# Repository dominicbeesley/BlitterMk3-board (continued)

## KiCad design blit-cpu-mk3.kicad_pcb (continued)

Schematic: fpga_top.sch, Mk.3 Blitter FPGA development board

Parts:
U8: 10M16DCF256I7G_mk3pinstest; MAX10_FBGA_256_dom

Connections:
/ALTERA_CONFIG_SEL: U8.F8 (~ALTERA_CONFIG_SEL~); also elsewhere on the board
/ALTERA_CONF_DONE: U8.E7 (~ALTERA_CONF_DONE~); also elsewhere on the board
/ALTERA_nCONFIG: U8.E8 (~ALTERA_nCONFIG~); also elsewhere on the board
/ALTERA_nSTATUS: U8.F7 (~ALTERA_nSTATUS~); also elsewhere on the board
/CLK_48M: U8.J11 (CLK_48M_i); also elsewhere on the board
/HDMI_CKN: U8.P10 (HDMI_CK_o(n)); also elsewhere on the board
/HDMI_CKP: U8.P11 (HDMI_CK_o); also elsewhere on the board
/HDMI_D0N: U8.P13 (HDMI_D0_o(n)); also elsewhere on the board
/HDMI_D0P: U8.P12 (HDMI_D0_o); also elsewhere on the board
/HDMI_D1N: U8.M10 (HDMI_D1_o(n)); also elsewhere on the board
/HDMI_D1P: U8.L9 (HDMI_D1_o); also elsewhere on the board
/HDMI_D2N: U8.M11 (HDMI_D2_o(n)); also elsewhere on the board
/HDMI_D2P: U8.L10 (HDMI_D2_o); also elsewhere on the board
/HDMI_HPD: U8.T14 (HDMI_HPD_i); also elsewhere on the board
/HDMI_SCL: U8.T15 (HDMI_SCL_o); also elsewhere on the board
/HDMI_SDA: U8.R14 (HDMI_SDA_io); also elsewhere on the board
/I2C_SCL: U8.T8 (I2C_SCL_o); also elsewhere on the board
/I2C_SDA: U8.R9 (I2C_SDA_io); also elsewhere on the board
/MEM_FL_nCE: U8.B2 (MEM_FL_nCE_o); also elsewhere on the board
/MEM_RAM_nCE0: U8.F5 (MEM_RAM_nCE_o_0); also elsewhere on the board
/MEM_nOE: U8.C3 (MEM_nOE_o); also elsewhere on the board
/MEM_nWE: U8.K6 (MEM_nWE_o); also elsewhere on the board
/SD_CLK: U8.P9 (SD_CLK_o); also elsewhere on the board
/SD_CS: U8.R10 (SD_CS_o); also elsewhere on the board
/SD_DET: U8.T12 (SD_DET_i); also elsewhere on the board
/SD_MISO: U8.R11 (SD_MISO_i); also elsewhere on the board
/SD_MOSI: U8.T11 (SD_MOSI_o); also elsewhere on the board
/SND_L: U8.M9 (SND_L_o); also elsewhere on the board
/SND_R: U8.T9 (SND_R_o); also elsewhere on the board
/SUP_nRES: U8.R8 (SUP_nRESET_i); also elsewhere on the board
/SYS_BUFD_DIR: U8.E16 (SYS_BUF_D_DIR_o); also elsewhere on the board
/SYS_BUFD_nOE: U8.F14 (SYS_BUF_D_nOE_o); also elsewhere on the board
/SYS_DBE: U8.D16 (SYS_nDBE_i); also elsewhere on the board
/SYS_PHI0: U8.D15 (SYS_PHI0_i); also elsewhere on the board
/SYS_PHI1: U8.N16 (SYS_PHI1_o); also elsewhere on the board
/SYS_PHI2: U8.R15 (SYS_PHI2_o); also elsewhere on the board
/SYS_RDY: U8.C15 (SYS_RDY_i); also elsewhere on the board
/SYS_RnW: U8.M16 (SYS_RnW_o); also elsewhere on the board
/SYS_SYNC: U8.N14 (SYS_SYNC_o); also elsewhere on the board
/SYS_nIRQ: U8.C16 (SYS_nIRQ_i); also elsewhere on the board
/SYS_nNMI: U8.B15 (SYS_nNMI_i); also elsewhere on the board
/UI/LED0: U8.D14 (LED_o_0); also elsewhere on the board
/UI/LED1: U8.G11 (LED_o_1); also elsewhere on the board
/UI/LED2: U8.E14 (LED_o_2); also elsewhere on the board
/UI/LED3: U8.G12 (LED_o_3); also elsewhere on the board
/exp_PORTA_DIR: U8.C4 (exp_PORTA_DIR_o); also elsewhere on the board
/exp_PORTA_nOE: U8.C5 (exp_PORTA_nOE_o); also elsewhere on the board
/exp_PORTE_nOE: U8.A3 (exp_PORTE_nOE); also elsewhere on the board
/exp_PORTF_nOE: U8.B3 (exp_PORTF_nOE); also elsewhere on the board
/exp_PORTG_nOE: U8.B16 (exp_PORTG_nOE); also elsewhere on the board
/fpga_top/BTNUSER_i_0: U8.C14 (BTNUSER_i_0); also elsewhere on the board
/fpga_top/BTNUSER_i_1: U8.F12 (BTNUSER_i_1); also elsewhere on the board
/fpga_top/exp_PORTA_io_0: U8.C6 (exp_PORTA_io_0); also elsewhere on the board
/fpga_top/exp_PORTA_io_1: U8.E9 (exp_PORTA_io_1); also elsewhere on the board
/fpga_top/exp_PORTA_io_2: U8.F9 (exp_PORTA_io_2); also elsewhere on the board
/fpga_top/exp_PORTA_io_3: U8.C10 (exp_PORTA_io_3); also elsewhere on the board
/fpga_top/exp_PORTA_io_4: U8.E11 (exp_PORTA_io_4); also elsewhere on the board
/fpga_top/exp_PORTA_io_5: U8.C9 (exp_PORTA_io_5); also elsewhere on the board
/fpga_top/exp_PORTA_io_6: U8.D9 (exp_PORTA_io_6); also elsewhere on the board
/fpga_top/exp_PORTA_io_7: U8.B12 (exp_PORTA_io_7); also elsewhere on the board
/fpga_top/exp_PORTB_o_0: U8.C12 (exp_PORTB_o_0); also elsewhere on the board
/fpga_top/exp_PORTB_o_1: U8.D12 (exp_PORTB_o_1); also elsewhere on the board
/fpga_top/exp_PORTB_o_2: U8.C13 (exp_PORTB_o_2); also elsewhere on the board
/fpga_top/exp_PORTB_o_3: U8.A15 (exp_PORTB_o_3); also elsewhere on the board
/fpga_top/exp_PORTB_o_4: U8.A13 (exp_PORTB_o_4); also elsewhere on the board
/fpga_top/exp_PORTB_o_5: U8.B13 (exp_PORTB_o_5); also elsewhere on the board
/fpga_top/exp_PORTB_o_6: U8.A14 (exp_PORTB_o_6); also elsewhere on the board
/fpga_top/exp_PORTB_o_7: U8.F11 (exp_PORTB_o_7); also elsewhere on the board
/fpga_top/exp_PORTC_io_0: U8.R5 (exp_PORTC_io_0); also elsewhere on the board
/fpga_top/exp_PORTC_io_1: U8.T5 (exp_PORTC_io_1); also elsewhere on the board
/fpga_top/exp_PORTC_io_2: U8.R6 (exp_PORTC_io_2); also elsewhere on the board
/fpga_top/exp_PORTC_io_3: U8.R4 (exp_PORTC_io_3); also elsewhere on the board
/fpga_top/exp_PORTC_io_4: U8.T3 (exp_PORTC_io_4); also elsewhere on the board
/fpga_top/exp_PORTC_io_5: U8.T6 (exp_PORTC_io_5); also elsewhere on the board
/fpga_top/exp_PORTC_io_6: U8.R3 (exp_PORTC_io_6); also elsewhere on the board
/fpga_top/exp_PORTC_io_7: U8.T4 (exp_PORTC_io_7); also elsewhere on the board
/fpga_top/exp_PORTC_io_8: U8.P6 (exp_PORTC_io_8); also elsewhere on the board
/fpga_top/exp_PORTC_io_9: U8.P5 (exp_PORTC_io_9); also elsewhere on the board
/fpga_top/exp_PORTC_io_10: U8.P4 (exp_PORTC_io_10); also elsewhere on the board
/fpga_top/exp_PORTC_io_11: U8.N3 (exp_PORTC_io_11); also elsewhere on the board
/fpga_top/exp_PORTD_io_0: U8.N5 (exp_PORTD_io_0); also elsewhere on the board
/fpga_top/exp_PORTD_io_1: U8.N4 (exp_PORTD_io_1); also elsewhere on the board
/fpga_top/exp_PORTD_io_2: U8.R2 (exp_PORTD_io_2); also elsewhere on the board
/fpga_top/exp_PORTD_io_3: U8.M3 (exp_PORTD_io_3); also elsewhere on the board
/fpga_top/exp_PORTD_io_4: U8.M1 (exp_PORTD_io_4); also elsewhere on the board
/fpga_top/exp_PORTD_io_5: U8.M2 (exp_PORTD_io_5); also elsewhere on the board
/fpga_top/exp_PORTD_io_6: U8.T2 (exp_PORTD_io_6); also elsewhere on the board
/fpga_top/exp_PORTD_io_7: U8.N1 (exp_PORTD_io_7); also elsewhere on the board
/fpga_top/exp_PORTD_io_8: U8.N2 (exp_PORTD_io_8); also elsewhere on the board
/fpga_top/exp_PORTD_io_9: U8.R1 (exp_PORTD_io_9); also elsewhere on the board
/fpga_top/exp_PORTD_io_10: U8.P2 (exp_PORTD_io_10); also elsewhere on the board
/fpga_top/exp_PORTD_io_11: U8.P1 (exp_PORTD_io_11); also elsewhere on the board
/fpga_top/exp_PORTEFG_io_0: U8.A4 (exp_PORTEFG_io_0); also elsewhere on the board
/fpga_top/exp_PORTEFG_io_1: U8.B4 (exp_PORTEFG_io_1); also elsewhere on the board
/fpga_top/exp_PORTEFG_io_2: U8.A5 (exp_PORTEFG_io_2); also elsewhere on the board
/fpga_top/exp_PORTEFG_io_3: U8.B5 (exp_PORTEFG_io_3); also elsewhere on the board
/fpga_top/exp_PORTEFG_io_4: U8.A6 (exp_PORTEFG_io_4); also elsewhere on the board
/fpga_top/exp_PORTEFG_io_5: U8.B6 (exp_PORTEFG_io_5); also elsewhere on the board
/fpga_top/exp_PORTEFG_io_6: U8.A7 (exp_PORTEFG_io_6); also elsewhere on the board
/fpga_top/exp_PORTEFG_io_7: U8.B7 (exp_PORTEFG_io_7); also elsewhere on the board
/fpga_top/exp_PORTEFG_io_8: U8.A8 (exp_PORTEFG_io_8); also elsewhere on the board
/fpga_top/exp_PORTEFG_io_9: U8.B8 (exp_PORTEFG_io_9); also elsewhere on the board
/fpga_top/exp_PORTEFG_io_10: U8.A9 (exp_PORTEFG_io_10); also elsewhere on the board
/fpga_top/exp_PORTEFG_io_11: U8.B9 (exp_PORTEFG_io_11); also elsewhere on the board
/memory/MEM_A0: U8.F4 (MEM_A_o_0); also elsewhere on the board
/memory/MEM_A1: U8.G2 (MEM_A_o_1); also elsewhere on the board
/memory/MEM_A2: U8.J2 (MEM_A_o_2); also elsewhere on the board
/memory/MEM_A3: U8.J1 (MEM_A_o_3); also elsewhere on the board
/memory/MEM_A4: U8.L3 (MEM_A_o_4); also elsewhere on the board
/memory/MEM_A5: U8.L2 (MEM_A_o_5); also elsewhere on the board
/memory/MEM_A6: U8.L1 (MEM_A_o_6); also elsewhere on the board
/memory/MEM_A7: U8.L6 (MEM_A_o_7); also elsewhere on the board
/memory/MEM_A8: U8.H5 (MEM_A_o_8); also elsewhere on the board
/memory/MEM_A9: U8.H6 (MEM_A_o_9); also elsewhere on the board
/memory/MEM_A10: U8.A2 (MEM_A_o_10); also elsewhere on the board
/memory/MEM_A11: U8.G5 (MEM_A_o_11); also elsewhere on the board
/memory/MEM_A12: U8.L7 (MEM_A_o_12); also elsewhere on the board
/memory/MEM_A13: U8.J6 (MEM_A_o_13); also elsewhere on the board
/memory/MEM_A14: U8.J5 (MEM_A_o_14); also elsewhere on the board
/memory/MEM_A15: U8.L8 (MEM_A_o_15); also elsewhere on the board
/memory/MEM_A16: U8.K2 (MEM_A_o_16); also elsewhere on the board
/memory/MEM_A17: U8.J3 (MEM_A_o_17); also elsewhere on the board
/memory/MEM_A18: U8.K5 (MEM_A_o_18); also elsewhere on the board
/memory/MEM_A19: U8.T7 (MEM_A_o_19); also elsewhere on the board
/memory/MEM_A20: U8.R7 (MEM_A_o_20); also elsewhere on the board
/memory/MEM_D0: U8.F1 (MEM_D_io_0); also elsewhere on the board
/memory/MEM_D1: U8.F2 (MEM_D_io_1); also elsewhere on the board
/memory/MEM_D2: U8.E1 (MEM_D_io_2); also elsewhere on the board
/memory/MEM_D3: U8.E3 (MEM_D_io_3); also elsewhere on the board
/memory/MEM_D4: U8.D1 (MEM_D_io_4); also elsewhere on the board
/memory/MEM_D5: U8.C1 (MEM_D_io_5); also elsewhere on the board
/memory/MEM_D6: U8.C2 (MEM_D_io_6); also elsewhere on the board
/memory/MEM_D7: U8.B1 (MEM_D_io_7); also elsewhere on the board
/memory/MEM_RAM_nCE1: U8.G6 (MEM_RAM_nCE_o_1); also elsewhere on the board
/memory/MEM_RAM_nCE2: U8.M6 (MEM_RAM_nCE_o_2); also elsewhere on the board
/memory/MEM_RAM_nCE3: U8.M8 (MEM_RAM_nCE_o_3); also elsewhere on the board
/sys_plug_and_buffers/SYS_A0: U8.M14 (SYS_A_o_0); also elsewhere on the board
/sys_plug_and_buffers/SYS_A1: U8.M15 (SYS_A_o_1); also elsewhere on the board
/sys_plug_and_buffers/SYS_A2: U8.L12 (SYS_A_o_2); also elsewhere on the board
/sys_plug_and_buffers/SYS_A3: U8.K14 (SYS_A_o_3); also elsewhere on the board
/sys_plug_and_buffers/SYS_A4: U8.L15 (SYS_A_o_4); also elsewhere on the board
/sys_plug_and_buffers/SYS_A5: U8.L16 (SYS_A_o_5); also elsewhere on the board
/sys_plug_and_buffers/SYS_A6: U8.K15 (SYS_A_o_6); also elsewhere on the board
/sys_plug_and_buffers/SYS_A7: U8.J15 (SYS_A_o_7); also elsewhere on the board
/sys_plug_and_buffers/SYS_A8: U8.H15 (SYS_A_o_8); also elsewhere on the board
/sys_plug_and_buffers/SYS_A9: U8.H16 (SYS_A_o_9); also elsewhere on the board
/sys_plug_and_buffers/SYS_A10: U8.J14 (SYS_A_o_10); also elsewhere on the board
/sys_plug_and_buffers/SYS_A11: U8.J16 (SYS_A_o_11); also elsewhere on the board
/sys_plug_and_buffers/SYS_A12: U8.L11 (SYS_A_o_12); also elsewhere on the board
/sys_plug_and_buffers/SYS_A13: U8.K12 (SYS_A_o_13); also elsewhere on the board
/sys_plug_and_buffers/SYS_A14: U8.K11 (SYS_A_o_14); also elsewhere on the board
/sys_plug_and_buffers/SYS_A15: U8.J12 (SYS_A_o_15); also elsewhere on the board
/sys_plug_and_buffers/SYS_AUX_IO_0: U8.A12 (SYS_AUX_io_0); also elsewhere on the board
/sys_plug_and_buffers/SYS_AUX_IO_1: U8.E10 (SYS_AUX_io_1); also elsewhere on the board
/sys_plug_and_buffers/SYS_AUX_IO_2: U8.B11 (SYS_AUX_io_2); also elsewhere on the board
/sys_plug_and_buffers/SYS_AUX_IO_3: U8.F10 (SYS_AUX_io_3); also elsewhere on the board
/sys_plug_and_buffers/SYS_AUX_IO_4: U8.A11 (SYS_AUX_io_4); also elsewhere on the board
/sys_plug_and_buffers/SYS_AUX_IO_5: U8.B10 (SYS_AUX_io_5); also elsewhere on the board
/sys_plug_and_buffers/SYS_AUX_IO_6: U8.A10 (SYS_AUX_io_6); also elsewhere on the board
/sys_plug_and_buffers/SYS_AUX_O0: U8.R16 (SYS_AUX_o_0); also elsewhere on the board
/sys_plug_and_buffers/SYS_AUX_O1: U8.P14 (SYS_AUX_o_1); also elsewhere on the board
/sys_plug_and_buffers/SYS_AUX_O2: U8.P16 (SYS_AUX_o_2); also elsewhere on the board
/sys_plug_and_buffers/SYS_AUX_O3: U8.P15 (SYS_AUX_o_3); also elsewhere on the board
/sys_plug_and_buffers/SYS_D0: U8.P8 (SYS_D_io_0); also elsewhere on the board
/sys_plug_and_buffers/SYS_D1: U8.H12 (SYS_D_io_1); also elsewhere on the board
/sys_plug_and_buffers/SYS_D2: U8.G14 (SYS_D_io_2); also elsewhere on the board
/sys_plug_and_buffers/SYS_D3: U8.H11 (SYS_D_io_3); also elsewhere on the board
/sys_plug_and_buffers/SYS_D4: U8.G16 (SYS_D_io_4); also elsewhere on the board
/sys_plug_and_buffers/SYS_D5: U8.G15 (SYS_D_io_5); also elsewhere on the board
/sys_plug_and_buffers/SYS_D6: U8.F16 (SYS_D_io_6); also elsewhere on the board
/sys_plug_and_buffers/SYS_D7: U8.E15 (SYS_D_io_7); also elsewhere on the board

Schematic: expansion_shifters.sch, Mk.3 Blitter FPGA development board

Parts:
C511, C512, C521, C522, C531, C541, C551: 100n; C_0805
U51, U52: 74LVC4245A; TSSOP-24_4.4x7.8mm_Pitch0.65mm
U53, U54, U55: 74CB3T16211; TSSOP-56_6.1x14mm_Pitch0.5mm

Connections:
+3V3: C512.1, C522.1, C531.1, C541.1, C551.1, U51.23 (VCCb), U51.24 (VCCb), U52.23 (VCCb), U52.24 (VCCb), U53.17 (Vcc), U54.17 (Vcc), U55.17 (Vcc); also elsewhere on the board
+5V: C511.1, C521.1, U51.1 (VCCa), U52.1 (VCCa); also elsewhere on the board
/exp_PORTA_DIR: U51.2 (A->B); also elsewhere on the board
/exp_PORTA_nOE: U51.22 (CE); also elsewhere on the board
/exp_PORTE_nOE: U55.55 (2nOE); also elsewhere on the board
/exp_PORTF_nOE: U55.56 (1nOE); also elsewhere on the board
/exp_PORTG_nOE: U54.55 (2nOE); also elsewhere on the board
/expansion_headers/5C_exp_PORTA0: U51.3 (A0); also elsewhere on the board
/expansion_headers/5C_exp_PORTA1: U51.4 (A1); also elsewhere on the board
/expansion_headers/5C_exp_PORTA2: U51.7 (A4); also elsewhere on the board
/expansion_headers/5C_exp_PORTA3: U51.8 (A5); also elsewhere on the board
/expansion_headers/5C_exp_PORTA4: U51.10 (A7); also elsewhere on the board
/expansion_headers/5C_exp_PORTA5: U51.5 (A2); also elsewhere on the board
/expansion_headers/5C_exp_PORTA6: U51.6 (A3); also elsewhere on the board
/expansion_headers/5C_exp_PORTA7: U51.9 (A6); also elsewhere on the board
/expansion_headers/5C_exp_PORTB0: U52.4 (A1); also elsewhere on the board
/expansion_headers/5C_exp_PORTB1: U52.6 (A3); also elsewhere on the board
/expansion_headers/5C_exp_PORTB2: U52.8 (A5); also elsewhere on the board
/expansion_headers/5C_exp_PORTB3: U52.10 (A7); also elsewhere on the board
/expansion_headers/5C_exp_PORTB4: U52.3 (A0); also elsewhere on the board
/expansion_headers/5C_exp_PORTB5: U52.5 (A2); also elsewhere on the board
/expansion_headers/5C_exp_PORTB6: U52.7 (A4); also elsewhere on the board
/expansion_headers/5C_exp_PORTB7: U52.9 (A6); also elsewhere on the board
/expansion_headers/5_exp_PORTC0: U53.5 (1A4); also elsewhere on the board
/expansion_headers/5_exp_PORTC1: U53.4 (1A3); also elsewhere on the board
/expansion_headers/5_exp_PORTC2: U53.3 (1A2); also elsewhere on the board
/expansion_headers/5_exp_PORTC3: U53.7 (1A6); also elsewhere on the board
/expansion_headers/5_exp_PORTC4: U53.9 (1A7); also elsewhere on the board
/expansion_headers/5_exp_PORTC5: U53.2 (1A1); also elsewhere on the board
/expansion_headers/5_exp_PORTC6: U53.10 (1A8); also elsewhere on the board
/expansion_headers/5_exp_PORTC7: U53.6 (1A5); also elsewhere on the board
/expansion_headers/5_exp_PORTC8: U53.11 (1A9); also elsewhere on the board
/expansion_headers/5_exp_PORTC9: U53.12 (1A10); also elsewhere on the board
/expansion_headers/5_exp_PORTC10: U53.13 (1A11); also elsewhere on the board
/expansion_headers/5_exp_PORTC11: U53.16 (2A2); also elsewhere on the board
/expansion_headers/5_exp_PORTD0: U53.14 (1A12); also elsewhere on the board
/expansion_headers/5_exp_PORTD1: U53.15 (2A1); also elsewhere on the board
/expansion_headers/5_exp_PORTD2: U53.21 (2A5); also elsewhere on the board
/expansion_headers/5_exp_PORTD3: U53.18 (2A3); also elsewhere on the board
/expansion_headers/5_exp_PORTD4: U53.28 (2A12); also elsewhere on the board
/expansion_headers/5_exp_PORTD5: U53.27 (2A11); also elsewhere on the board
/expansion_headers/5_exp_PORTD6: U53.20 (2A4); also elsewhere on the board
/expansion_headers/5_exp_PORTD7: U53.26 (2A10); also elsewhere on the board
/expansion_headers/5_exp_PORTD8: U53.25 (2A9); also elsewhere on the board
/expansion_headers/5_exp_PORTD9: U53.22 (2A6); also elsewhere on the board
/expansion_headers/5_exp_PORTD10: U53.23 (2A7); also elsewhere on the board
/expansion_headers/5_exp_PORTD11: U53.24 (2A8); also elsewhere on the board
/expansion_headers/5_exp_PORTE0: U55.28 (2A12); also elsewhere on the board
/expansion_headers/5_exp_PORTE1: U55.27 (2A11); also elsewhere on the board
/expansion_headers/5_exp_PORTE2: U55.26 (2A10); also elsewhere on the board
/expansion_headers/5_exp_PORTE3: U55.25 (2A9); also elsewhere on the board
/expansion_headers/5_exp_PORTE4: U55.24 (2A8); also elsewhere on the board
/expansion_headers/5_exp_PORTE5: U55.23 (2A7); also elsewhere on the board
/expansion_headers/5_exp_PORTE6: U55.22 (2A6); also elsewhere on the board
/expansion_headers/5_exp_PORTE7: U55.21 (2A5); also elsewhere on the board
/expansion_headers/5_exp_PORTE8: U55.20 (2A4); also elsewhere on the board
/expansion_headers/5_exp_PORTE9: U55.18 (2A3); also elsewhere on the board
/expansion_headers/5_exp_PORTE10: U55.16 (2A2); also elsewhere on the board
/expansion_headers/5_exp_PORTE11: U55.15 (2A1); also elsewhere on the board
/expansion_headers/5_exp_PORTF0: U55.2 (1A1); also elsewhere on the board
/expansion_headers/5_exp_PORTF1: U55.3 (1A2); also elsewhere on the board
/expansion_headers/5_exp_PORTF2: U55.4 (1A3); also elsewhere on the board
/expansion_headers/5_exp_PORTF3: U55.5 (1A4); also elsewhere on the board
/expansion_headers/5_exp_PORTF4: U55.6 (1A5); also elsewhere on the board
/expansion_headers/5_exp_PORTF5: U55.7 (1A6); also elsewhere on the board
/expansion_headers/5_exp_PORTF6: U55.9 (1A7); also elsewhere on the board
/expansion_headers/5_exp_PORTF7: U55.10 (1A8); also elsewhere on the board
/expansion_headers/5_exp_PORTF8: U55.11 (1A9); also elsewhere on the board
/expansion_headers/5_exp_PORTF9: U55.12 (1A10); also elsewhere on the board
/expansion_headers/5_exp_PORTF10: U55.13 (1A11); also elsewhere on the board
/expansion_headers/5_exp_PORTF11: U55.14 (1A12); also elsewhere on the board
/expansion_headers/5_exp_PORTG0: U54.28 (2A12); also elsewhere on the board
/expansion_headers/5_exp_PORTG1: U54.27 (2A11); also elsewhere on the board
/expansion_headers/5_exp_PORTG2: U54.26 (2A10); also elsewhere on the board
/expansion_headers/5_exp_PORTG3: U54.25 (2A9); also elsewhere on the board
/expansion_headers/5_exp_PORTG4: U54.24 (2A8); also elsewhere on the board
/expansion_headers/5_exp_PORTG5: U54.23 (2A7); also elsewhere on the board
/expansion_headers/5_exp_PORTG6: U54.22 (2A6); also elsewhere on the board
/expansion_headers/5_exp_PORTG7: U54.21 (2A5); also elsewhere on the board
/expansion_headers/5_exp_PORTG8: U54.20 (2A4); also elsewhere on the board
/expansion_headers/5_exp_PORTG9: U54.18 (2A3); also elsewhere on the board
/expansion_headers/5_exp_PORTG10: U54.16 (2A2); also elsewhere on the board
/expansion_headers/5_exp_PORTG11: U54.15 (2A1); also elsewhere on the board
/fpga_top/exp_PORTA_io_0: U51.21 (B0); also elsewhere on the board
/fpga_top/exp_PORTA_io_1: U51.20 (B1); also elsewhere on the board
/fpga_top/exp_PORTA_io_2: U51.17 (B4); also elsewhere on the board
/fpga_top/exp_PORTA_io_3: U51.16 (B5); also elsewhere on the board
/fpga_top/exp_PORTA_io_4: U51.14 (B7); also elsewhere on the board
/fpga_top/exp_PORTA_io_5: U51.19 (B2); also elsewhere on the board
/fpga_top/exp_PORTA_io_6: U51.18 (B3); also elsewhere on the board
/fpga_top/exp_PORTA_io_7: U51.15 (B6); also elsewhere on the board
/fpga_top/exp_PORTB_o_0: U52.20 (B1); also elsewhere on the board
/fpga_top/exp_PORTB_o_1: U52.18 (B3); also elsewhere on the board
/fpga_top/exp_PORTB_o_2: U52.16 (B5); also elsewhere on the board
/fpga_top/exp_PORTB_o_3: U52.14 (B7); also elsewhere on the board
/fpga_top/exp_PORTB_o_4: U52.21 (B0); also elsewhere on the board
/fpga_top/exp_PORTB_o_5: U52.19 (B2); also elsewhere on the board
/fpga_top/exp_PORTB_o_6: U52.17 (B4); also elsewhere on the board
/fpga_top/exp_PORTB_o_7: U52.15 (B6); also elsewhere on the board
/fpga_top/exp_PORTC_io_0: U53.51 (1B4); also elsewhere on the board
/fpga_top/exp_PORTC_io_1: U53.52 (1B3); also elsewhere on the board
/fpga_top/exp_PORTC_io_2: U53.53 (1B2); also elsewhere on the board
/fpga_top/exp_PORTC_io_3: U53.48 (1B6); also elsewhere on the board
/fpga_top/exp_PORTC_io_4: U53.47 (1B7); also elsewhere on the board
/fpga_top/exp_PORTC_io_5: U53.54 (1B1); also elsewhere on the board
/fpga_top/exp_PORTC_io_6: U53.46 (1B8); also elsewhere on the board
/fpga_top/exp_PORTC_io_7: U53.50 (1B5); also elsewhere on the board
/fpga_top/exp_PORTC_io_8: U53.45 (1B9); also elsewhere on the board
/fpga_top/exp_PORTC_io_9: U53.44 (1B10); also elsewhere on the board
/fpga_top/exp_PORTC_io_10: U53.43 (1B11); also elsewhere on the board
/fpga_top/exp_PORTC_io_11: U53.40 (2B2); also elsewhere on the board
/fpga_top/exp_PORTD_io_0: U53.42 (1B12); also elsewhere on the board
/fpga_top/exp_PORTD_io_1: U53.41 (2B1); also elsewhere on the board
/fpga_top/exp_PORTD_io_2: U53.36 (2B5); also elsewhere on the board
/fpga_top/exp_PORTD_io_3: U53.39 (2B3); also elsewhere on the board
/fpga_top/exp_PORTD_io_4: U53.29 (2B12); also elsewhere on the board
/fpga_top/exp_PORTD_io_5: U53.30 (2B11); also elsewhere on the board
/fpga_top/exp_PORTD_io_6: U53.37 (2B4); also elsewhere on the board
/fpga_top/exp_PORTD_io_7: U53.31 (2B10); also elsewhere on the board
/fpga_top/exp_PORTD_io_8: U53.32 (2B9); also elsewhere on the board
/fpga_top/exp_PORTD_io_9: U53.35 (2B6); also elsewhere on the board
/fpga_top/exp_PORTD_io_10: U53.34 (2B7); also elsewhere on the board
/fpga_top/exp_PORTD_io_11: U53.33 (2B8); also elsewhere on the board
/fpga_top/exp_PORTEFG_io_0: U54.29 (2B12), U55.29 (2B12), U55.54 (1B1); also elsewhere on the board
/fpga_top/exp_PORTEFG_io_1: U54.30 (2B11), U55.30 (2B11), U55.53 (1B2); also elsewhere on the board
/fpga_top/exp_PORTEFG_io_2: U54.31 (2B10), U55.31 (2B10), U55.52 (1B3); also elsewhere on the board
/fpga_top/exp_PORTEFG_io_3: U54.32 (2B9), U55.32 (2B9), U55.51 (1B4); also elsewhere on the board
/fpga_top/exp_PORTEFG_io_4: U54.33 (2B8), U55.33 (2B8), U55.50 (1B5); also elsewhere on the board
/fpga_top/exp_PORTEFG_io_5: U54.34 (2B7), U55.34 (2B7), U55.48 (1B6); also elsewhere on the board
/fpga_top/exp_PORTEFG_io_6: U54.35 (2B6), U55.35 (2B6), U55.47 (1B7); also elsewhere on the board
/fpga_top/exp_PORTEFG_io_7: U54.36 (2B5), U55.36 (2B5), U55.46 (1B8); also elsewhere on the board
/fpga_top/exp_PORTEFG_io_8: U54.37 (2B4), U55.37 (2B4), U55.45 (1B9); also elsewhere on the board
/fpga_top/exp_PORTEFG_io_9: U54.39 (2B3), U55.39 (2B3), U55.44 (1B10); also elsewhere on the board
/fpga_top/exp_PORTEFG_io_10: U54.40 (2B2), U55.40 (2B2), U55.43 (1B11); also elsewhere on the board
/fpga_top/exp_PORTEFG_io_11: U54.41 (2B1), U55.41 (2B1), U55.42 (1B12); also elsewhere on the board

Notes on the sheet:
NOTE:U54B is on SYS schema

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
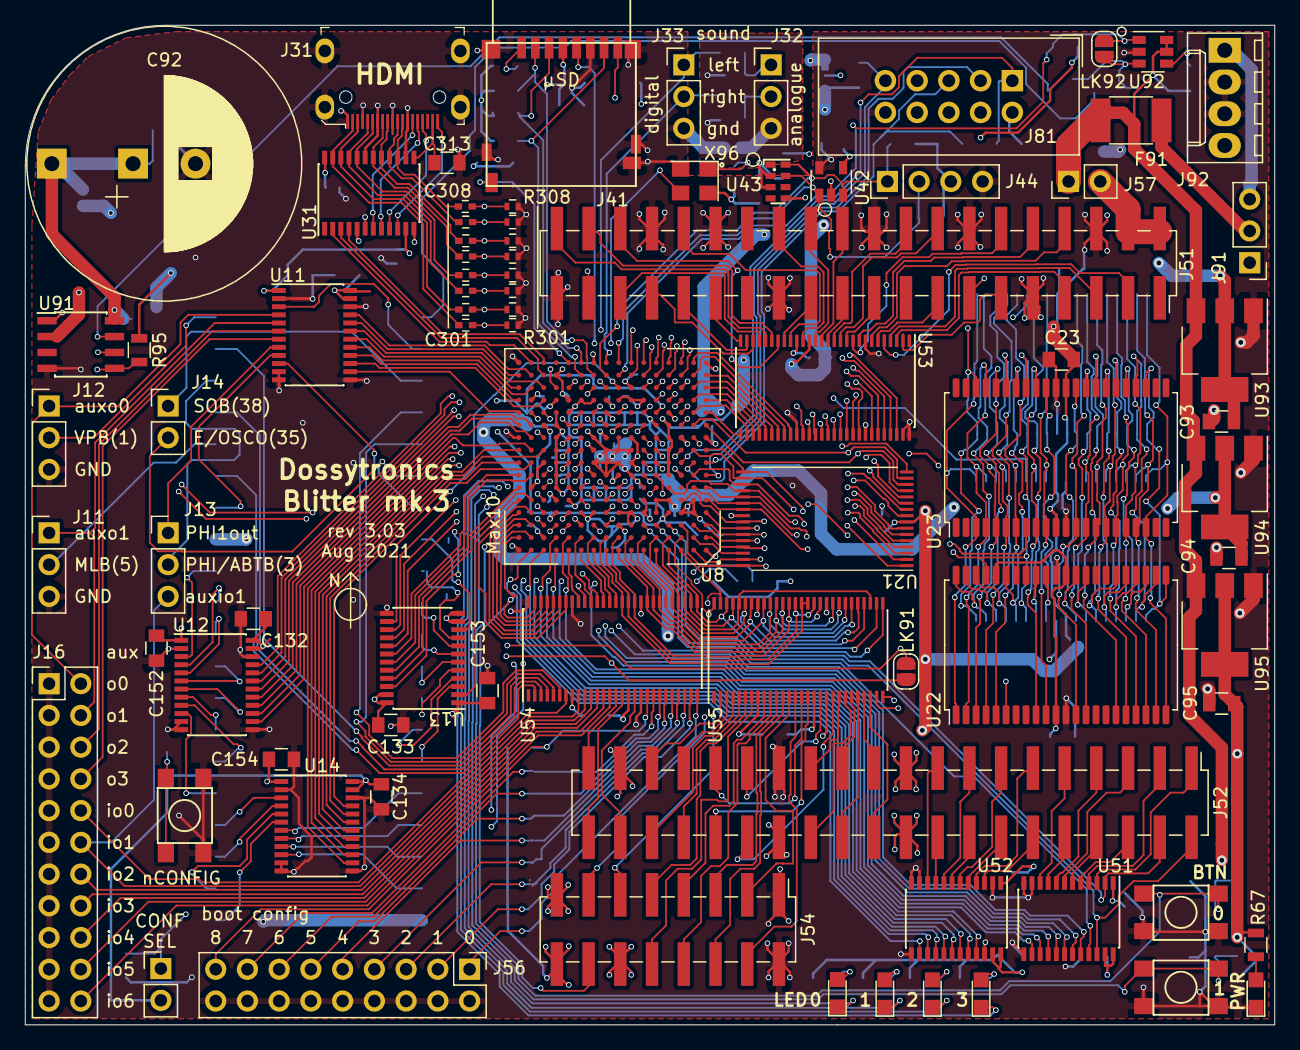
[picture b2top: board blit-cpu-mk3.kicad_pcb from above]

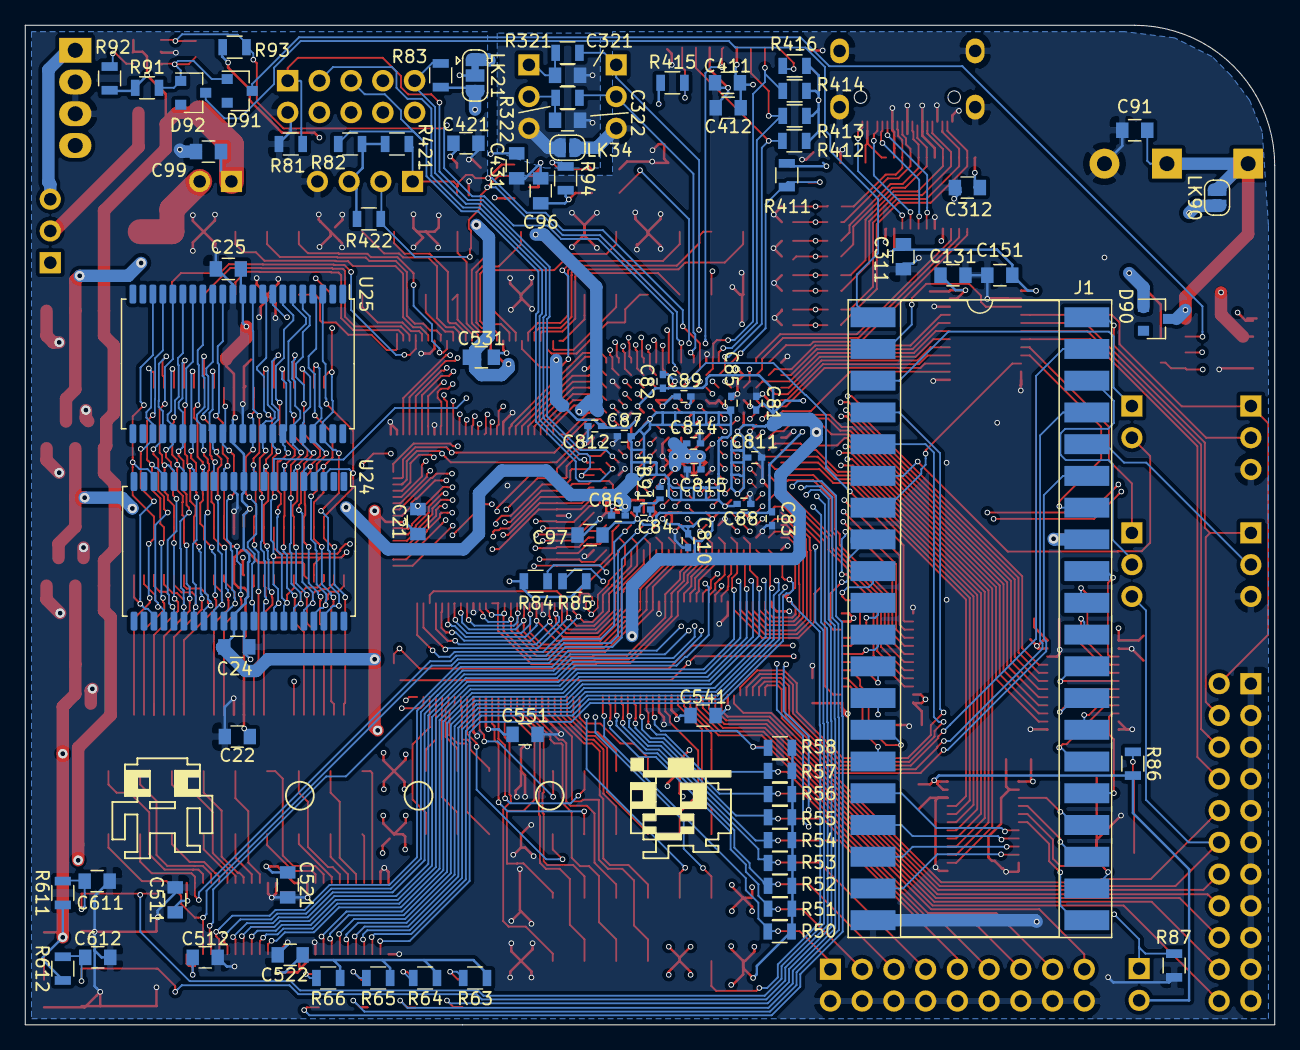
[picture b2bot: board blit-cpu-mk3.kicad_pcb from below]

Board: 4 copper layers, 100.0 x 80.0 mm, 169 parts (87 on the bottom side), 342 nets.

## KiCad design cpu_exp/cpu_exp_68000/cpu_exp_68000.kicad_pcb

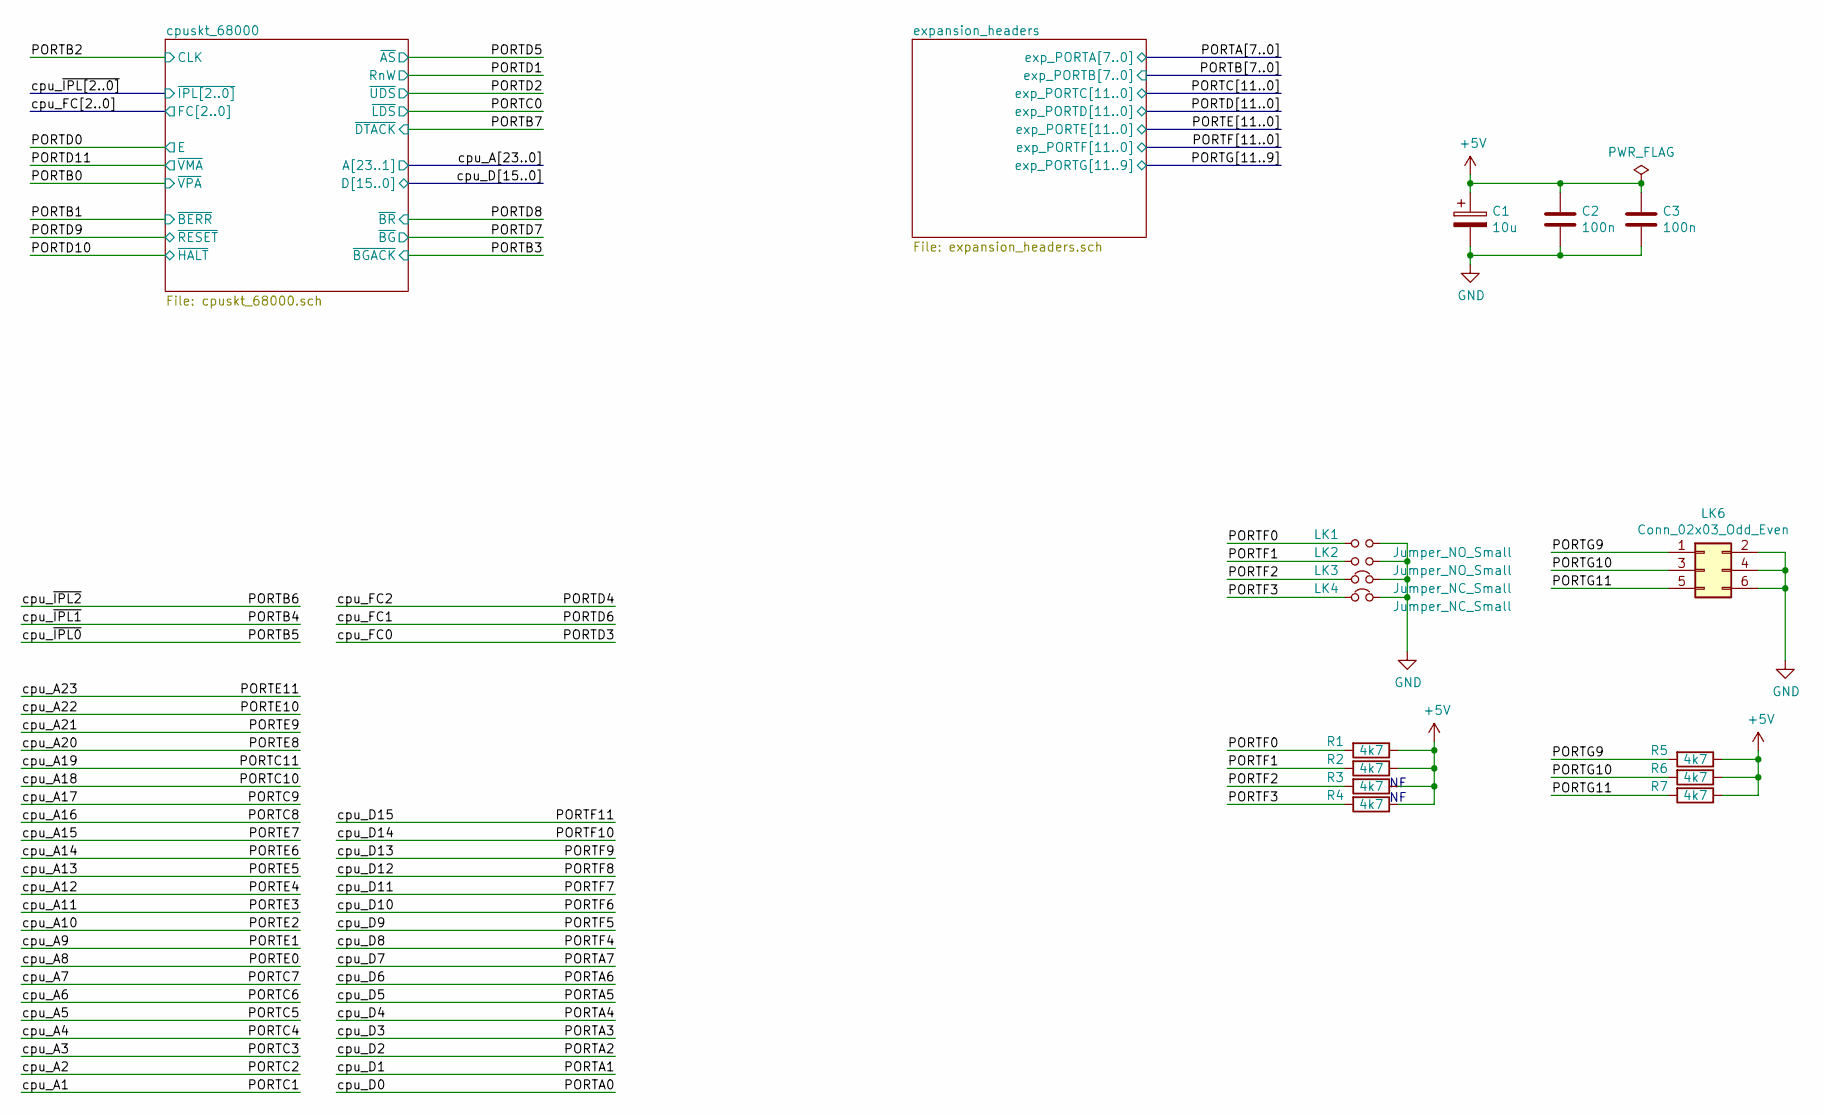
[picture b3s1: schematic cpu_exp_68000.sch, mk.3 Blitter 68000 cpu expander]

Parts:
C1: 10u; C_1206
C2, C3: 100n; C_0805
LK1, LK2: Jumper_NO_Small; SolderJumper-2_P1.3mm_Open_RoundedPad1.0x1.5mm-domsmallctyd
LK3, LK4: Jumper_NC_Small; SolderJumper-2_P1.3mm_Closed_RoundedPad1.0x1.5mm-domsmallct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
LK6: Conn_02x03_Odd_Even; PinHeader_2x03_P2.54mm_Vertical
R1, R2, R3, R4, R5, R6, R7: 4k7; R_0805

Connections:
+5V: C1.1, C2.1, C3.1, R1.1, R2.1, R3.1, R4.1, R5.1, R6.1, R7.1; also elsewhere on the board
/PORTF0: LK1.1, R1.2; also elsewhere on the board
/PORTF1: LK2.1, R2.2; also elsewhere on the board
/PORTF2: LK3.1, R3.2; also elsewhere on the board
/PORTF3: LK4.1, R4.2; also elsewhere on the board
/PORTG9: LK6.1, R5.2; also elsewhere on the board
/PORTG10: LK6.3, R6.2; also elsewhere on the board
/PORTG11: LK6.5, R7.2; also elsewhere on the board
GND: C1.2, C2.2, C3.2, LK1.2, LK2.2, LK3.2, LK4.2, LK6.2, LK6.4, LK6.6; also elsewhere on the board

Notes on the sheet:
NF NF
